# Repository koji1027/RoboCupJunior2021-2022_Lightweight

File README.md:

# RoboCupJunior2023_Lightweight
 高崎高校物理部 ロボカップジュニア2023 ライトウェイト部門

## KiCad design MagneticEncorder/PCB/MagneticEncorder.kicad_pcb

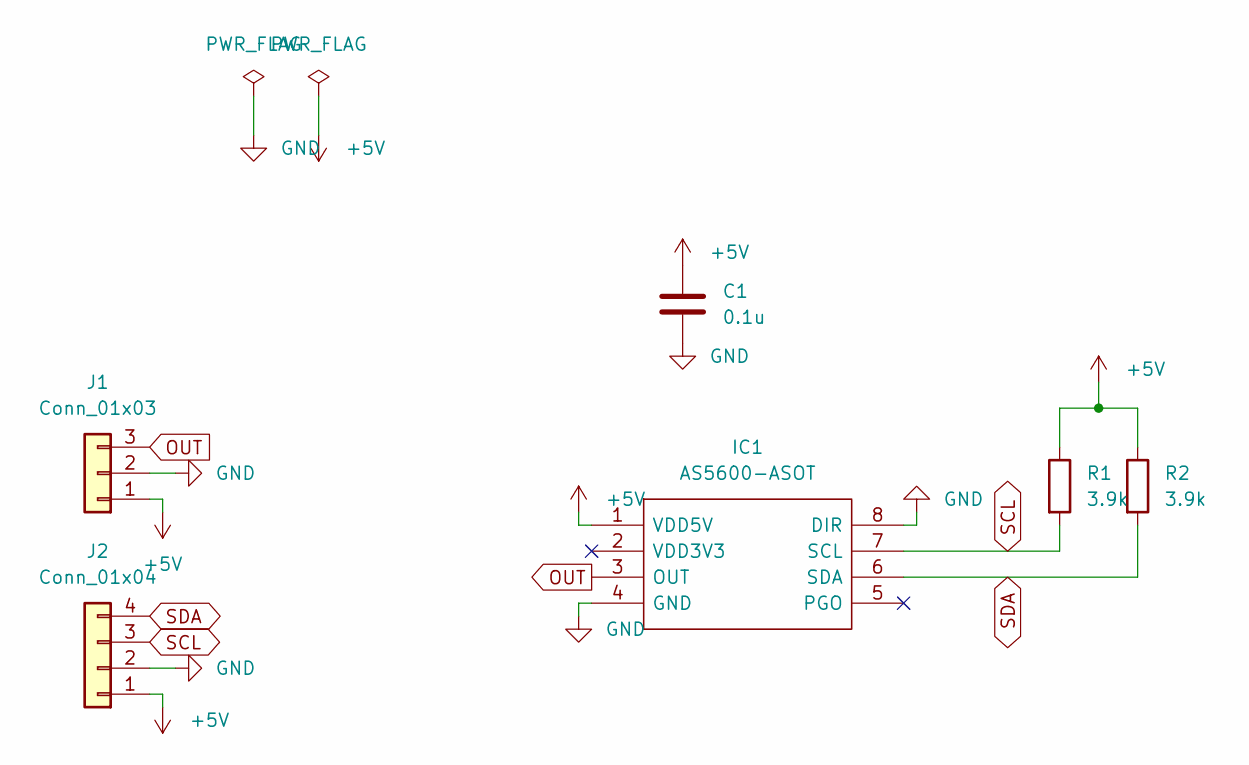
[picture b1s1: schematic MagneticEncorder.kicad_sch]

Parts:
C1: 0.1u; C_Disc_D5.1mm_W3.2mm_P5.00mm
IC1: AS5600-ASOT; SOIC127P600X175-8N; Manufacturer_Part_Number AS5600-ASOT; Mouser Part Number 985-AS5600-ASOT
J1: Conn_01x03; PinSocket_1x03_P2.54mm_Vertical
J2: Conn_01x04; PinSocket_1x04_P2.54mm_Vertical
R1, R2: 3.9k; R_Axial_DIN0204_L3.6mm_D1.6mm_P5.08mm_Horizontal

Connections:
+5V: C1.1, IC1.1 (VDD5V), J1.1, J2.1, R1.1, R2.1
GND: C1.2, IC1.4 (GND), IC1.8 (DIR), J1.2, J2.2
OUT: IC1.3 (OUT), J1.3
SCL: IC1.7 (SCL), J2.3, R1.2
SDA: IC1.6 (SDA), J2.4, R2.2

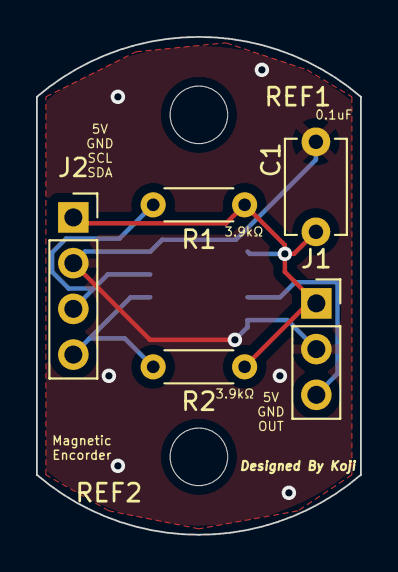
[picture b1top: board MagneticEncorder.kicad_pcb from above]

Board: 2 copper layers, 18.0 x 27.7 mm, 8 parts (1 on the bottom side), 5 nets.

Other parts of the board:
REF1, REF2: MountingHole_3.2mm_M3

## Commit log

2022-02-26 Magnetic Encorder PCB
    Magnetic Encorder PCB
2022-02-26 磁気式エンコーダ PCB基板
    磁気式エンコーダ PCB基板
2022-02-26 磁気式エンコーダ 3Dモデル
    磁気式エンコーダ 3Dモデル
2022-03-26 磁気式エンコーダ
2022-03-26 いろいろ
2022-03-26 いろいろ
    いろいろ
2022-04-04 やっと動いたやつ(BLDC)
    ああｌｆじせぎおえｗｊｇせｊふぉｒｗｋｐろｒｋｗくぉふぇおぎじじょｗじえりじょえｊごうぃｒじぇｊ
